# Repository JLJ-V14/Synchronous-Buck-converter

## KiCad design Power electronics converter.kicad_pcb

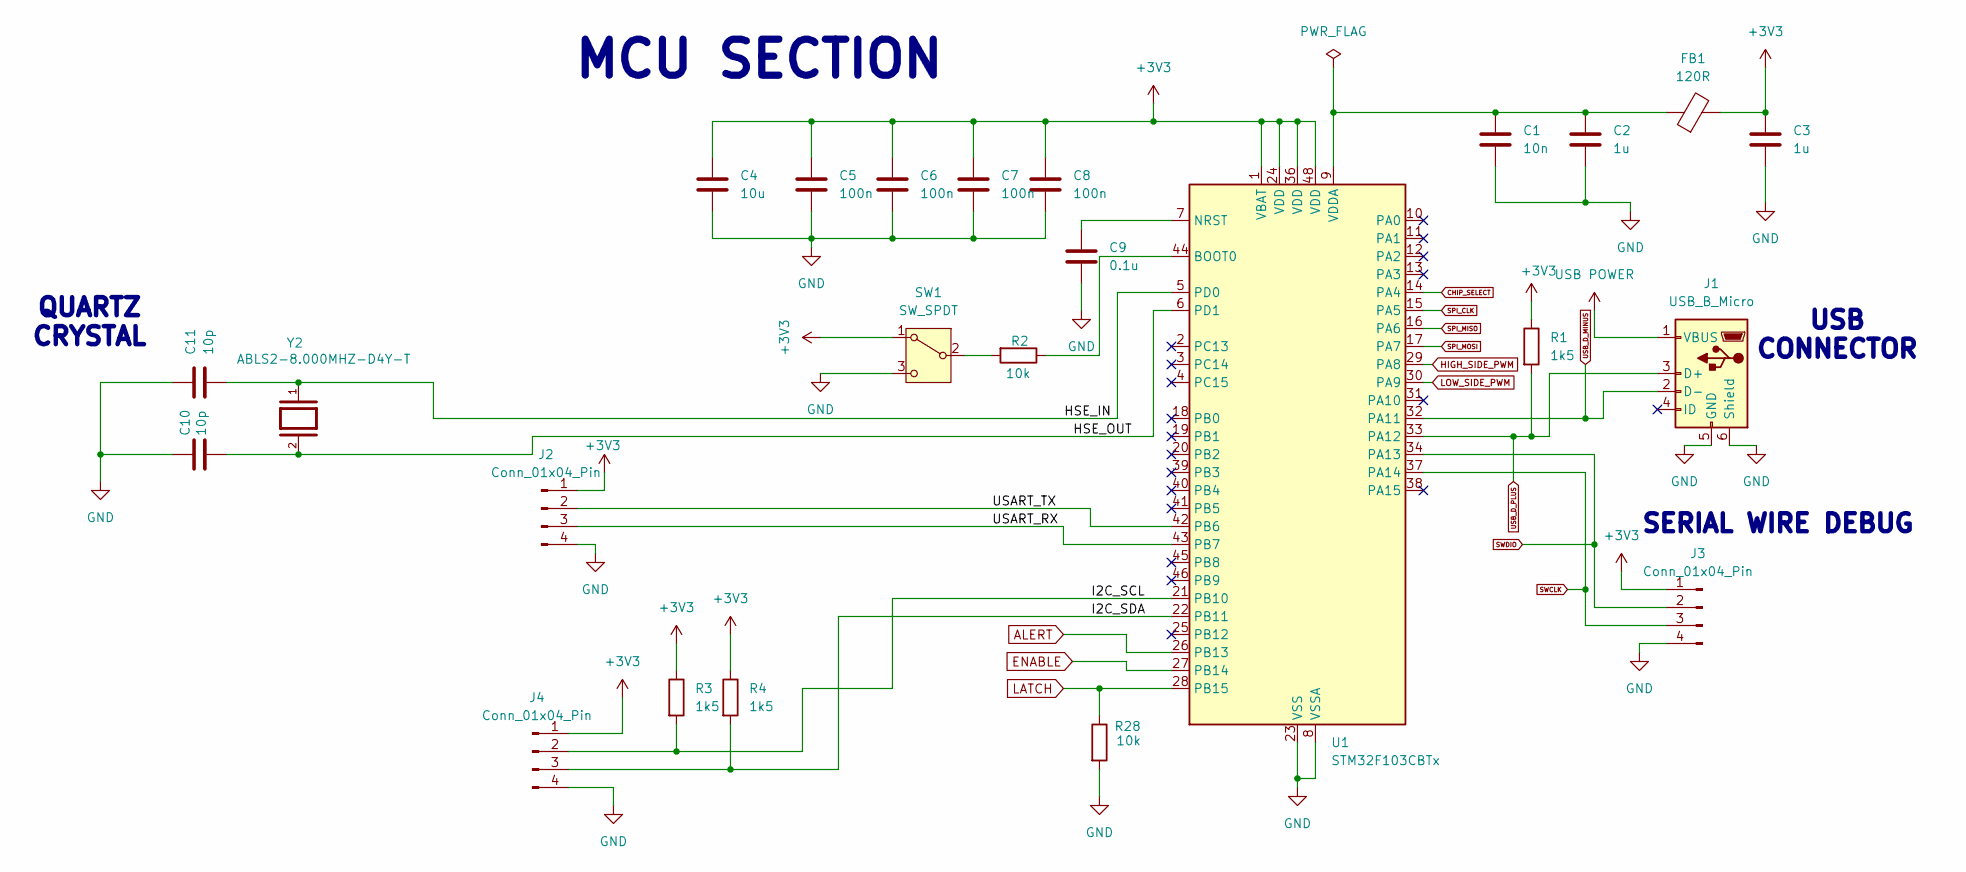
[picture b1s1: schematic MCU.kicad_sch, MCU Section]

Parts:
C1: 10n; C_0603_1608Metric
C2, C3: 1u; C_0603_1608Metric
C4: 10u; C_0603_1608Metric
C5, C6, C7, C8: 100n; C_0603_1608Metric
C9: 0.1u; C_0603_1608Metric
C10, C11: 10p; C_0603_1608Metric_Pad1.08x0.95mm_HandSolder
FB1: 120R; R_0805_2012Metric_Pad1.20x1.40mm_HandSolder
J1: USB_B_Micro; CONN_10118194-0001LF_AMP
J2, J3, J4: Conn_01x04_Pin; PinHeader_1x04_P2.54mm_Vertical
R1, R3, R4: 1k5; R_01005_0402Metric_Pad0.57x0.30mm_HandSolder
R2: 10k; R_0603_1608Metric_Pad0.98x0.95mm_HandSolder
R28: 10k; R_0402_1005Metric_Pad0.72x0.64mm_HandSolder
SW1: SW_SPDT; CON64_2X32_TU_HTS_SAI_CUSTOM
U1: STM32F103CBTx; LQFP-48_7x7mm_P0.5mm
Y2: ABLS2-8.000MHZ-D4Y-T; XTAL_ABLS2-8.000MHZ-D4Y-T; PARTREV 11.15.2016

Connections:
+3V3: C3.1, C4.1, C5.1, C6.1, C7.1, C8.1, FB1.2, J2.1, J3.1, J4.1, R1.1, R3.1, R4.1, SW1.1 (A), U1.1 (VBAT), U1.24 (VDD), U1.36 (VDD), U1.48 (VDD); also elsewhere on the board
/MCU Section/HSE_IN: C11.2, U1.5 (PD0), Y2.1
/MCU Section/HSE_OUT: C10.2, U1.6 (PD1), Y2.2
/MCU Section/I2C_SCL: J4.2, R3.2, U1.21 (PB10)
/MCU Section/I2C_SDA: J4.3, R4.2, U1.22 (PB11)
/MCU Section/USART_RX: J2.3, U1.43 (PB7)
/MCU Section/USART_TX: J2.2, U1.42 (PB6)
ALERT: U1.26 (PB13); also elsewhere on the board
CHIP_SELECT: U1.14 (PA4); also elsewhere on the board
ENABLE: U1.27 (PB14); also elsewhere on the board
GND: C1.2, C2.2, C3.2, C4.2, C5.2, C6.2, C7.2, C8.2, C9.2, C10.1, C11.1, J1.5 (GND), J1.6 (Shield), J2.4, J3.4, J4.4, R28.2, SW1.3 (C), U1.8 (VSSA), U1.23 (VSS), U1.35 (VSS), U1.47 (VSS); also elsewhere on the board
HIGH_SIDE_PWM: U1.29 (PA8); also elsewhere on the board
LATCH: R28.1, U1.28 (PB15); also elsewhere on the board
LOW_SIDE_PWM: U1.30 (PA9); also elsewhere on the board
unnamed: R2.2, SW1.2 (B)
unnamed: R2.1, U1.44 (BOOT0)
unnamed: C9.1, U1.7 (NRST)
unnamed: C1.1, C2.1, FB1.1, U1.9 (VDDA)
SPI_CLK: U1.15 (PA5); also elsewhere on the board
SPI_MISO: U1.16 (PA6); also elsewhere on the board
SPI_MOSI: U1.17 (PA7); also elsewhere on the board
SWCLK: J3.3, U1.37 (PA14)
SWDIO: J3.2, U1.34 (PA13)
USB POWER: J1.1 (VBUS); also elsewhere on the board
USB_D_MINUS: J1.2 (D-), U1.32 (PA11)
USB_D_PLUS: J1.3 (D+), R1.2, U1.33 (PA12)

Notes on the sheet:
QUARTZ CRYSTAL
MCU SECTION
SERIAL WIRE DEBUG
USB CONNECTOR

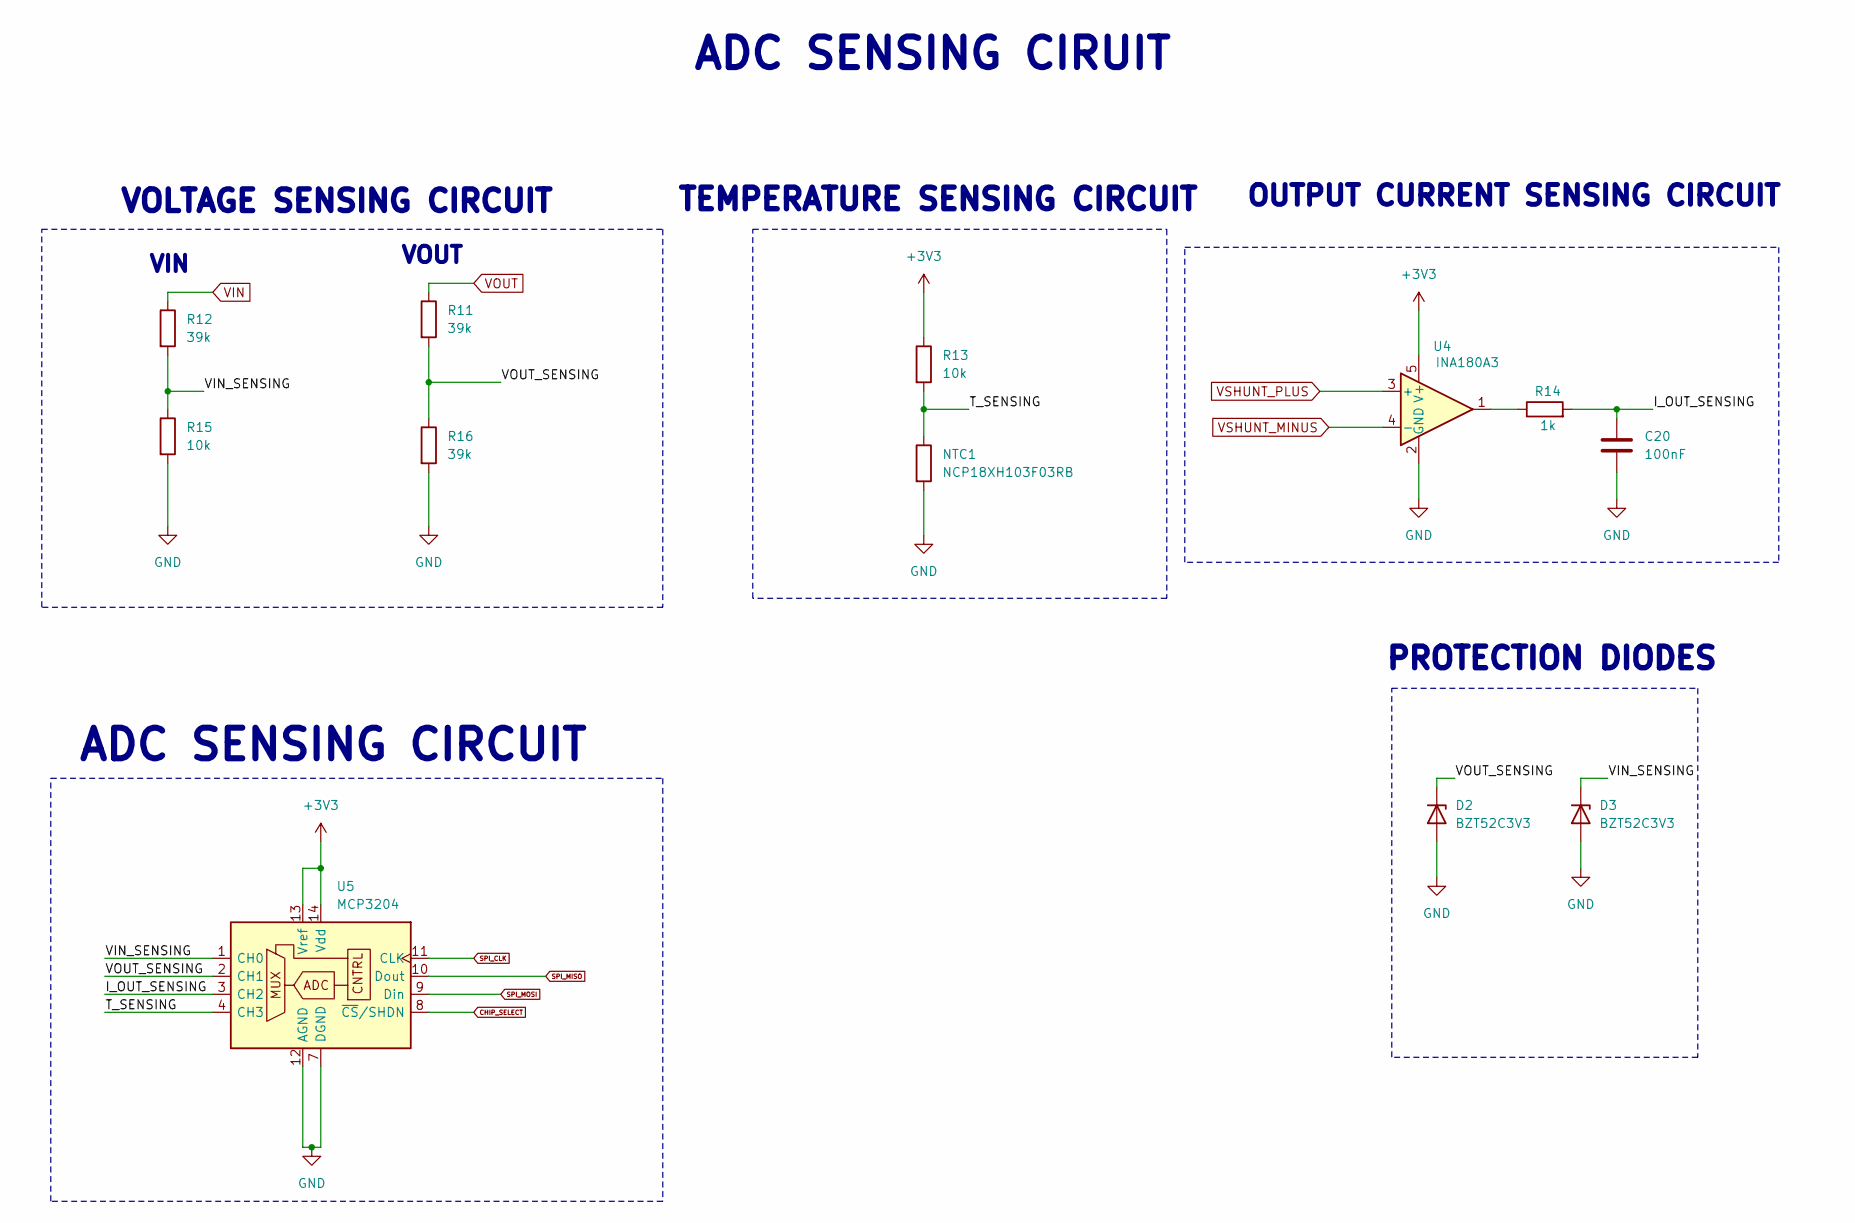
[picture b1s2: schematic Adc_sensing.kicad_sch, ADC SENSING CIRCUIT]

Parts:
C20: 100nF; C_0603_1608Metric_Pad1.08x0.95mm_HandSolder
D2, D3: BZT52C3V3; D_SOD-123F
NTC1: NCP18XH103F03RB; R_0603_1608Metric_Pad0.98x0.95mm_HandSolder
R11, R12, R16: 39k; R_0805_2012Metric_Pad1.20x1.40mm_HandSolder
R13, R15: 10k; R_0603_1608Metric_Pad0.98x0.95mm_HandSolder
R14: 1k; R_0603_1608Metric_Pad0.98x0.95mm_HandSolder
U4: INA180A3; SOT-23-5
U5: MCP3204; SOIC-14_3.9x8.7mm_P1.27mm

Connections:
+3V3: R13.1, U4.5 (V+), U5.13 (Vref), U5.14 (Vdd); also elsewhere on the board
/ADC sensing/I_OUT_SENSING: C20.1, R14.2, U5.3 (CH2)
/ADC sensing/T_SENSING: NTC1.1, R13.2, U5.4 (CH3)
/ADC sensing/VIN_SENSING: D3.1 (K), R12.2, R15.1, U5.1 (CH0)
/ADC sensing/VOUT_SENSING: D2.1 (K), R11.2, R16.1, U5.2 (CH1)
CHIP_SELECT: U5.8 (~CS/SHDN); also elsewhere on the board
GND: C20.2, D2.2 (A), D3.2 (A), NTC1.2, R15.2, R16.2, U4.2 (GND), U5.7 (DGND), U5.12 (AGND); also elsewhere on the board
unnamed: R14.1, U4.1
SPI_CLK: U5.11 (CLK); also elsewhere on the board
SPI_MISO: U5.10 (Dout); also elsewhere on the board
SPI_MOSI: U5.9 (Din); also elsewhere on the board
VIN: R12.1; also elsewhere on the board
VOUT: R11.1, U4.4 (-); also elsewhere on the board
VSHUNT_PLUS: U4.3 (+); also elsewhere on the board

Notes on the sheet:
ADC SENSING CIRCUIT
VOLTAGE SENSING CIRCUIT
VIN
TEMPERATURE SENSING CIRCUIT
PROTECTION DIODES
VOUT
OUTPUT CURRENT SENSING CIRCUIT
ADC SENSING CIRUIT

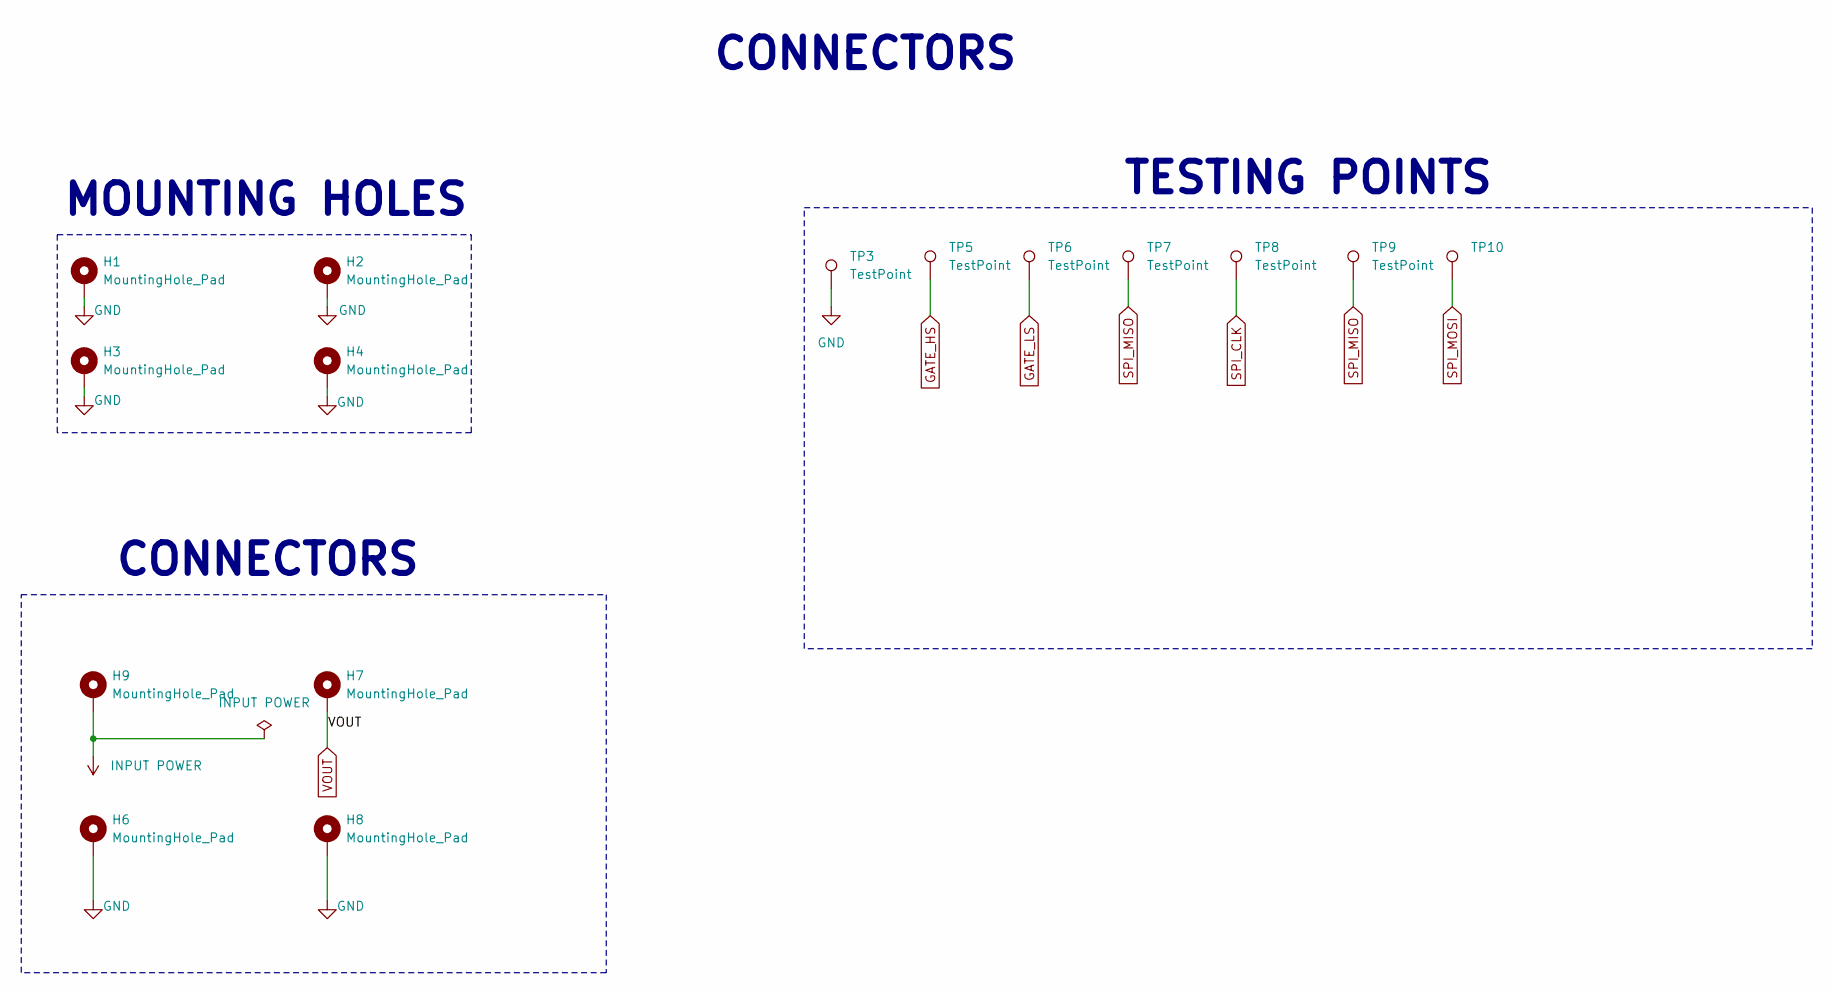
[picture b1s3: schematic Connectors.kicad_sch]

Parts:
H1, H2, H3, H4: MountingHole_Pad; MountingHole_3.2mm_M3_Pad
H6, H7, H8, H9: MountingHole_Pad; MountingHole_6.4mm_M6_ISO14580_Pad
TP3, TP5, TP6, TP7, TP8, TP9, TP10: TestPoint; TestPoint_Loop_D2.50mm_Drill1.0mm

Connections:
GATE_LS: TP6.1; also elsewhere on the board
GND: H1.1, H2.1, H3.1, H4.1, H6.1, H8.1, TP3.1; also elsewhere on the board
INPUT POWER: H9.1; also elsewhere on the board
unnamed: TP7.1, TP9.1
VOUT: H7.1; also elsewhere on the board

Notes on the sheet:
MOUNTING HOLES
CONNECTORS
CONNECTORS
TESTING POINTS

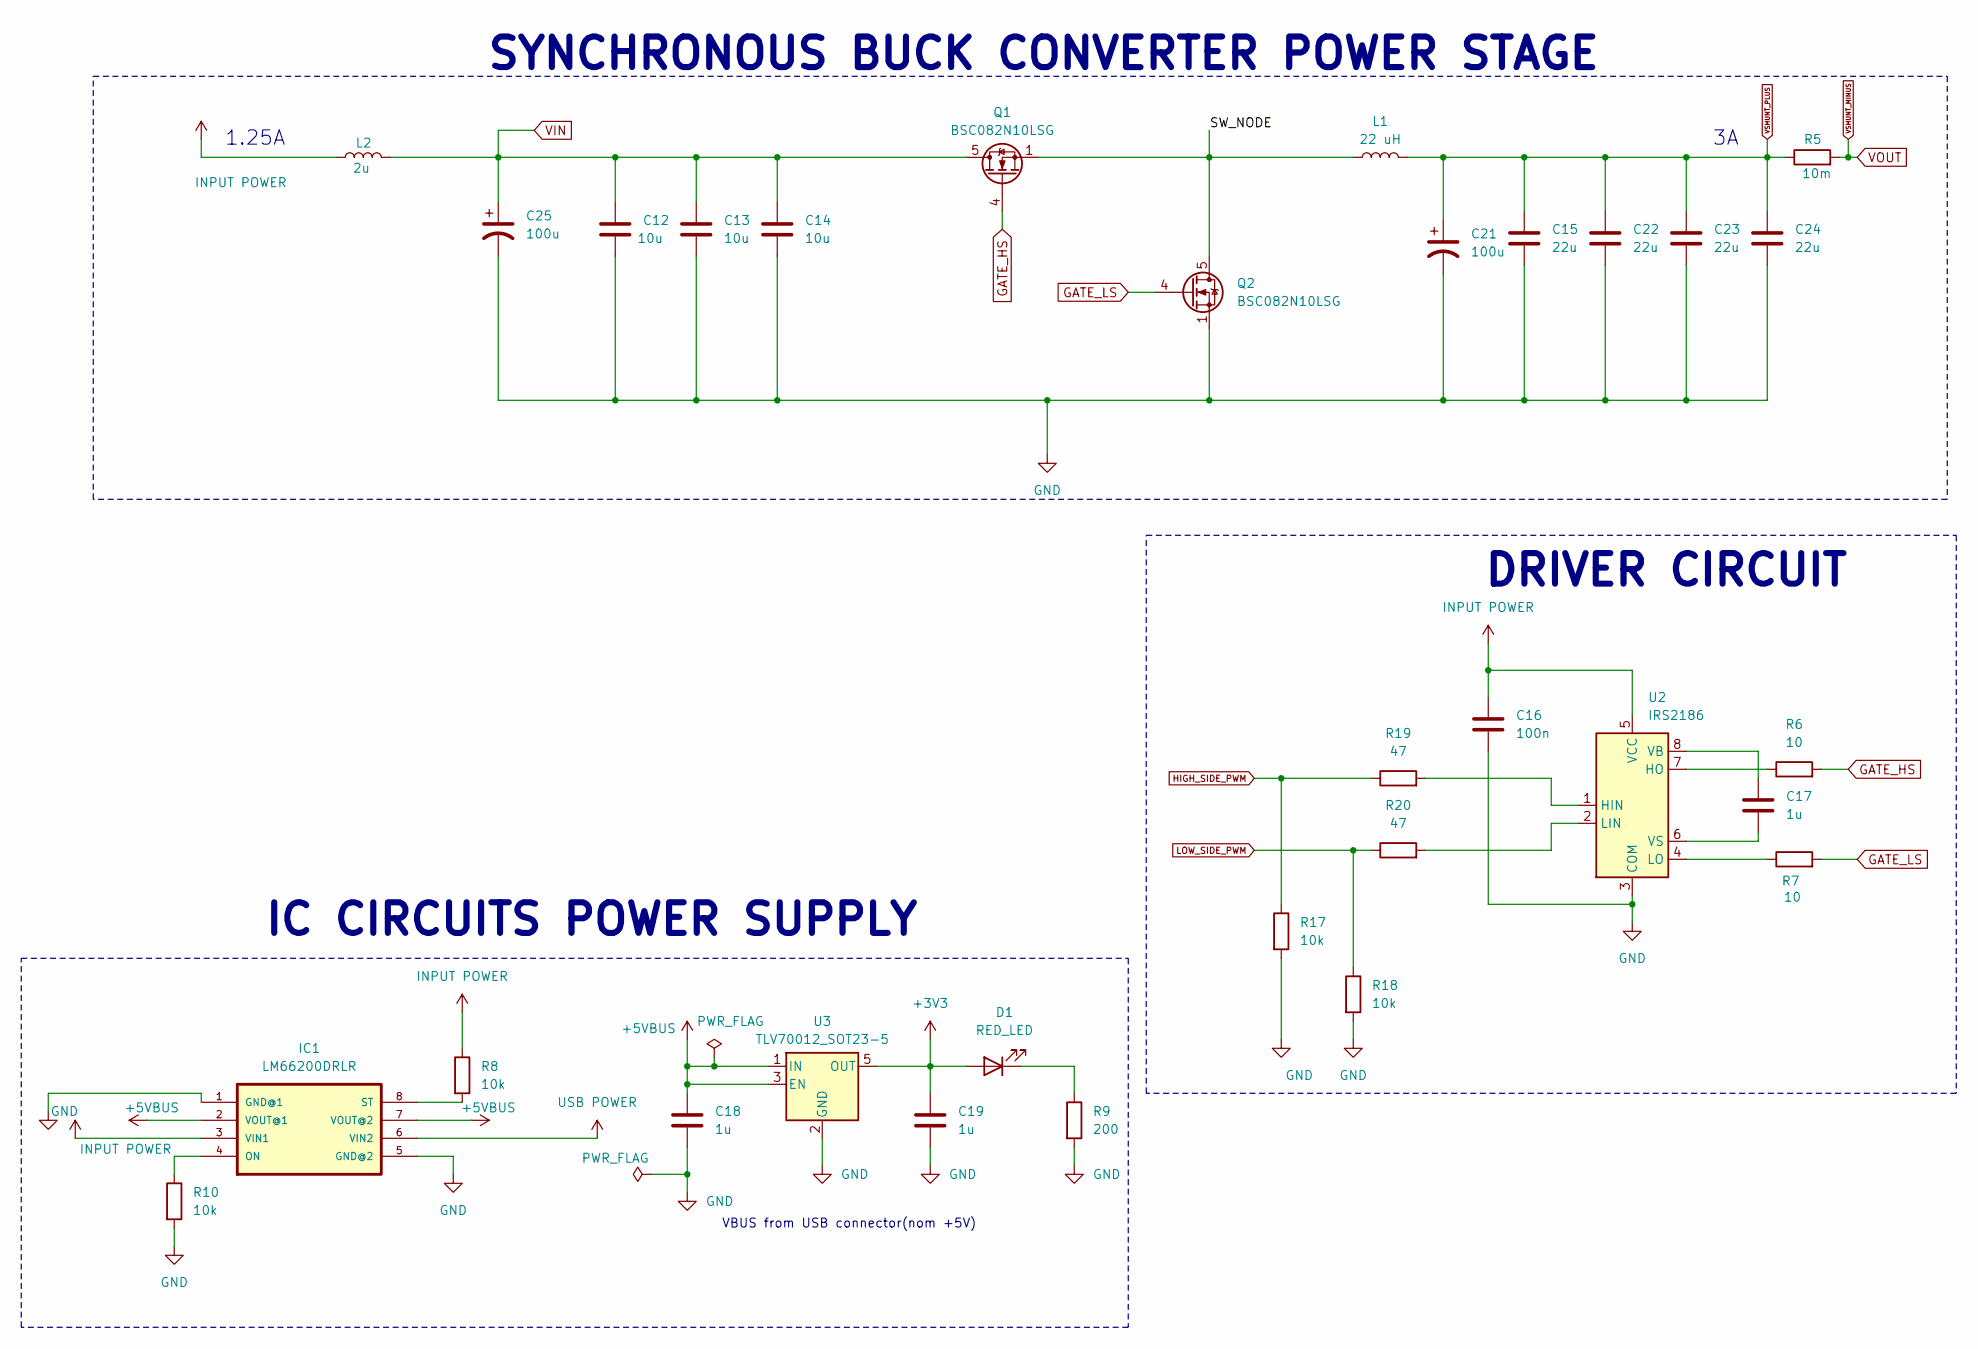
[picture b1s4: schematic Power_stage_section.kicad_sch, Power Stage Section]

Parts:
C12, C13, C14: 10u; C_0603_1608Metric_Pad1.08x0.95mm_HandSolder
C15, C22, C23, C24: 22u; C_0603_1608Metric_Pad1.08x0.95mm_HandSolder
C16: 100n; C_0603_1608Metric_Pad1.08x0.95mm_HandSolder
C17: 1u; C_0603_1608Metric_Pad1.08x0.95mm_HandSolder
C18, C19: 1u; C_0603_1608Metric
C21: 100u; C_1206_3216Metric_Pad1.33x1.80mm_HandSolder
C25: 100u; CP_Elec_6.3x5.7
D1: RED_LED; LED_0805_2012Metric_Pad1.15x1.40mm_HandSolder
IC1: LM66200DRLR; SOT-583-8
L1: 22 uH; INDUCTOR_TDK_BUCK
L2: 2u; SC63CB
Q1, Q2: BSC082N10LSG; TDSON-8-1
R5: 10m; R_0603_1608Metric_Pad0.98x0.95mm_HandSolder
R6, R7: 10; R_0805_2012Metric_Pad1.20x1.40mm_HandSolder
R8, R10, R17, R18: 10k; R_0603_1608Metric_Pad0.98x0.95mm_HandSolder
R9: 200; R_1206_3216Metric_Pad1.30x1.75mm_HandSolder
R19, R20: 47; R_0402_1005Metric_Pad0.72x0.64mm_HandSolder
U2: IRS2186; SOIC-8-1EP_3.9x4.9mm_P1.27mm_EP2.29x3mm
U3: TLV70012_SOT23-5; SOT-23-5

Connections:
+3V3: C19.1, D1.2 (A), U3.5 (OUT); also elsewhere on the board
+5VBUS: C18.1, IC1.2 (VOUT@1), IC1.7 (VOUT@2), U3.1 (IN), U3.3 (EN)
/Power Stage Section/SW_NODE: L1.1, Q1.1 (S), Q1.2 (S), Q1.3 (S), Q2.5 (D)
GATE_HS: Q1.4 (G), R6.2
GATE_LS: Q2.4 (G), R7.2; also elsewhere on the board
GND: C12.2, C13.2, C14.2, C15.2, C16.2, C18.2, C19.2, C21.2, C22.2, C23.2, C24.2, C25.2, IC1.1 (GND@1), IC1.5 (GND@2), Q2.1 (S), Q2.2 (S), Q2.3 (S), R9.2, R10.2, R17.2, R18.2, U2.3 (COM), U3.2 (GND); also elsewhere on the board
HIGH_SIDE_PWM: R17.1, R19.1; also elsewhere on the board
INPUT POWER: C16.1, IC1.3 (VIN1), L2.1, R8.1, U2.5 (VCC); also elsewhere on the board
LOW_SIDE_PWM: R18.1, R20.1; also elsewhere on the board
unnamed: D1.1 (K), R9.1
unnamed: IC1.4 (ON), R10.1
unnamed: IC1.8 (ST), R8.2
unnamed: R19.2, U2.1 (HIN)
unnamed: R6.1, U2.7 (HO)
unnamed: R20.2, U2.2 (LIN)
unnamed: R7.1, U2.4 (LO)
unnamed: C17.1, U2.8 (VB)
unnamed: C17.2, U2.6 (VS)
USB POWER: IC1.6 (VIN2); also elsewhere on the board
VIN: C12.1, C13.1, C14.1, C25.1, L2.2, Q1.5 (D); also elsewhere on the board
VOUT: R5.2; also elsewhere on the board
VSHUNT_PLUS: C15.1, C21.1, C22.1, C23.1, C24.1, L1.2, R5.1; also elsewhere on the board

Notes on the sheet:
IC CIRCUITS POWER SUPPLY
DRIVER CIRCUIT
VBUS from USB connector(nom +5V)
SYNCHRONOUS BUCK CONVERTER POWER STAGE
1.25A

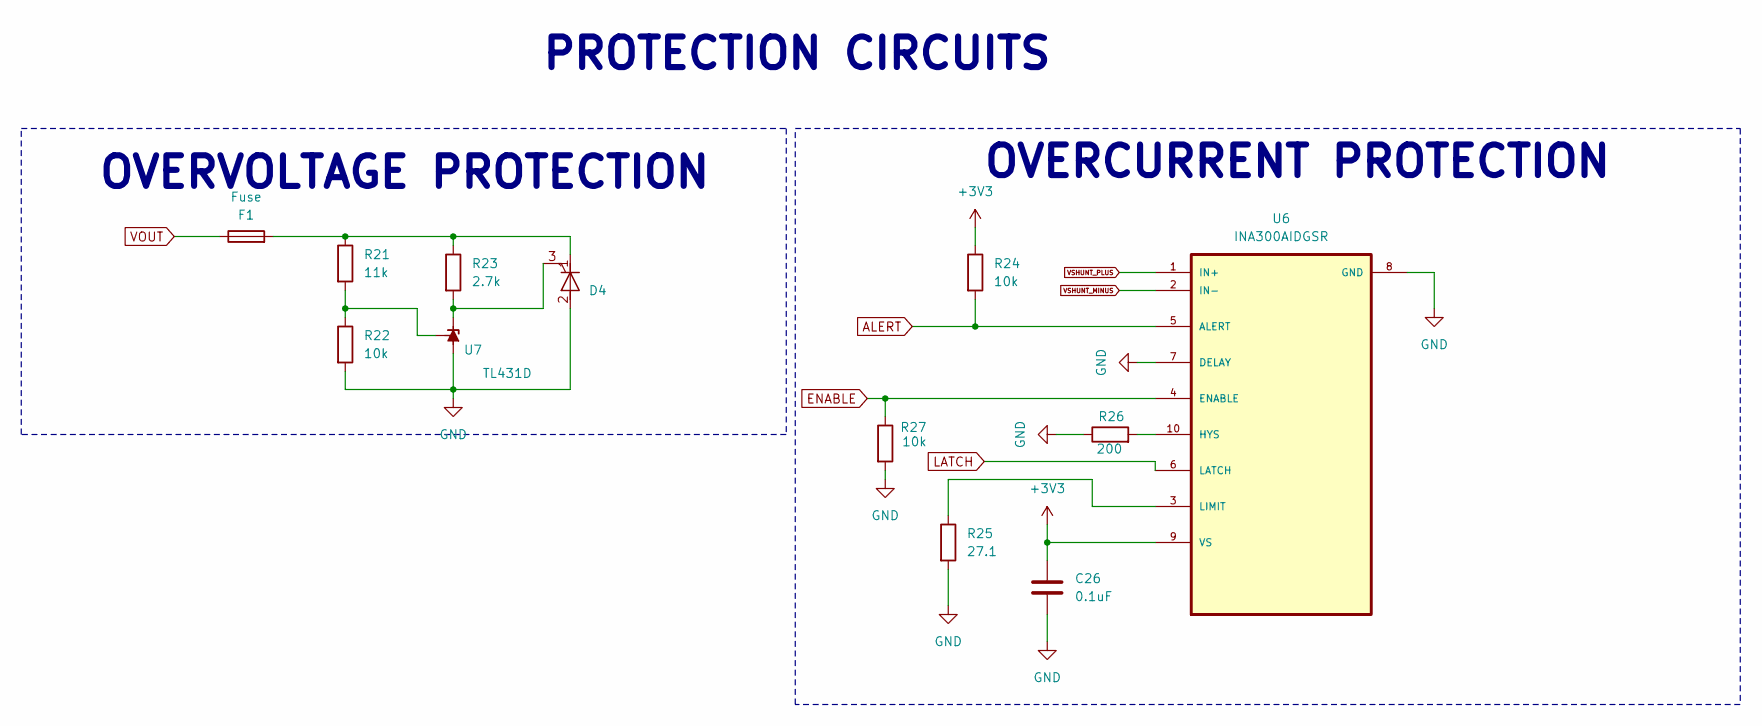
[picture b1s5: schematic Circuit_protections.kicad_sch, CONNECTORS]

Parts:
C26: 0.1uF; C_0603_1608Metric_Pad1.08x0.95mm_HandSolder
D4: Q_SCR_KAG; NYC222_THYRISTOR_FOOTPRINT
F1: Fuse; R_0603_1608Metric_Pad0.98x0.95mm_HandSolder
R21: 11k; R_0603_1608Metric_Pad0.98x0.95mm_HandSolder
R22: 10k; R_0603_1608Metric_Pad0.98x0.95mm_HandSolder
R23: 2.7k; R_0603_1608Metric_Pad0.98x0.95mm_HandSolder
R24, R27: 10k; R_0402_1005Metric_Pad0.72x0.64mm_HandSolder
R25: 27.1; R_0603_1608Metric_Pad0.98x0.95mm_HandSolder
R26: 200; R_0402_1005Metric_Pad0.72x0.64mm_HandSolder
U6: INA300AIDGSR; SOP50P490X110-10N-INA300
U7: TL431D; LM431

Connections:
+3V3: C26.1, R24.1, U6.9 (VS); also elsewhere on the board
ALERT: R24.2, U6.5 (ALERT); also elsewhere on the board
ENABLE: R27.1, U6.4 (ENABLE); also elsewhere on the board
GND: C26.2, D4.2 (A), R22.2, R25.2, R26.1, R27.2, U6.7 (DELAY), U6.8 (GND), U7.2 (A), U7.3 (A), U7.6 (A), U7.7 (A); also elsewhere on the board
LATCH: U6.6 (LATCH); also elsewhere on the board
unnamed: D4.3 (G), R23.2, U7.1 (K)
unnamed: D4.1 (K), F1.2, R21.1, R23.1
unnamed: R26.2, U6.10 (HYS)
unnamed: R25.1, U6.3 (LIMIT)
unnamed: R21.2, R22.1, U7.8 (REF)
VOUT: F1.1, U6.2 (IN-); also elsewhere on the board
VSHUNT_PLUS: U6.1 (IN+); also elsewhere on the board

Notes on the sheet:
PROTECTION CIRCUITS
OVERVOLTAGE PROTECTION
OVERCURRENT PROTECTION

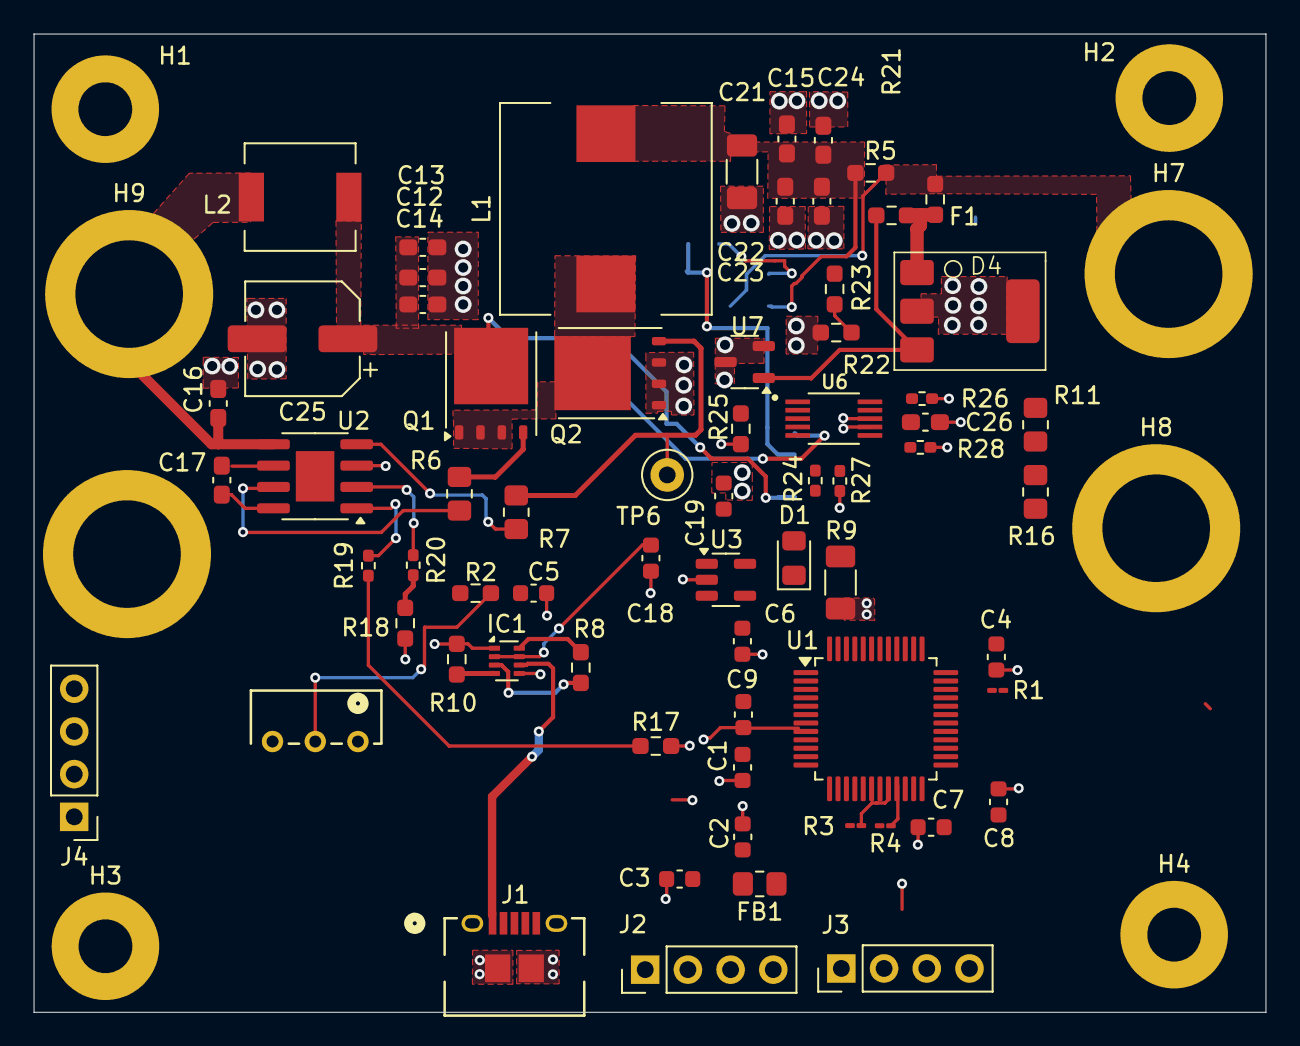
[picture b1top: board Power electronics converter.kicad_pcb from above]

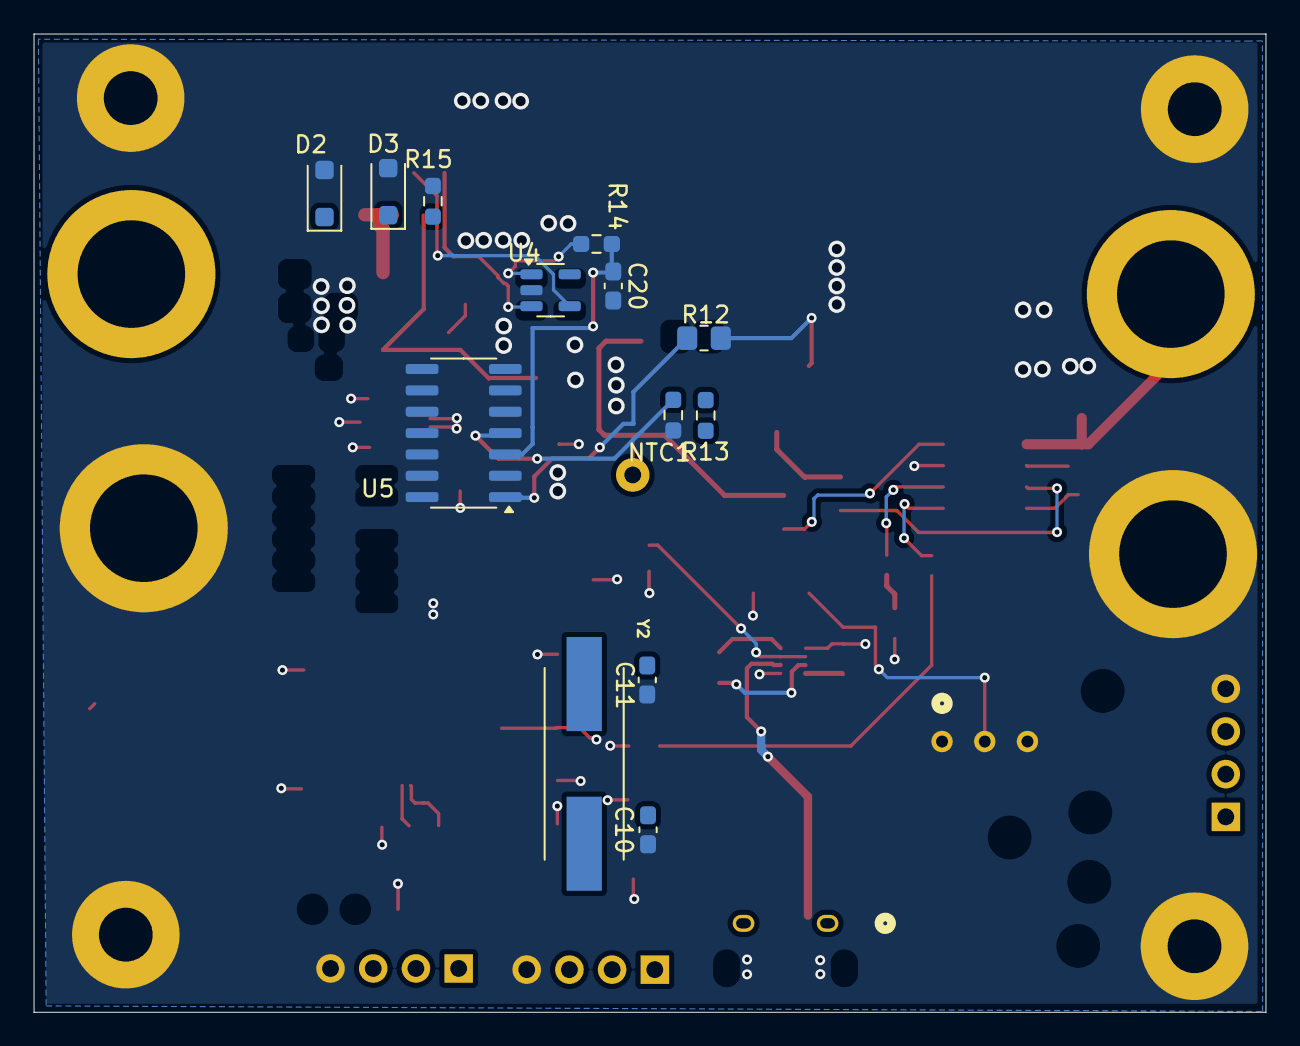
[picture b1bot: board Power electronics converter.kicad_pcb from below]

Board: 2 copper layers, 73.3 x 58.2 mm, 88 parts (13 on the bottom side), 53 nets.

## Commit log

2025-11-23 Initial commit: Synchronous buck converter project
2025-11-23 MCU Section partially finished
2025-12-31 Schematic finished pending of layout
2026-01-11 Commercial components selected
2026-02-04 over-voltage protection added
2026-03-01 Placement finished routing started
2026-03-01 Power loop routed
2026-03-10 Most of sensing routed
